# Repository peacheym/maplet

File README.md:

# Maplet

An ESP32 based eurorack module for libmapper connectivity.

## Why mappings in Eurorack?

Eurorack systems are excellent at making "generative music", where the system plays itself using sequencers, LFOs, clocks, and other modules. That said, there is lacking a method for "performative interaction" with Eurorack (asides from simply adjusting knobs directly on the system).

## Hardware

Maplet's front panel features a simple initial design.

## System Overview

The module uses an [UnexpectedMaker TinyPico](https://www.tinypico.com/) board based on the ESP32 chip as well as a MCP4728 digital-to-analog converter (DAC) as the main components.

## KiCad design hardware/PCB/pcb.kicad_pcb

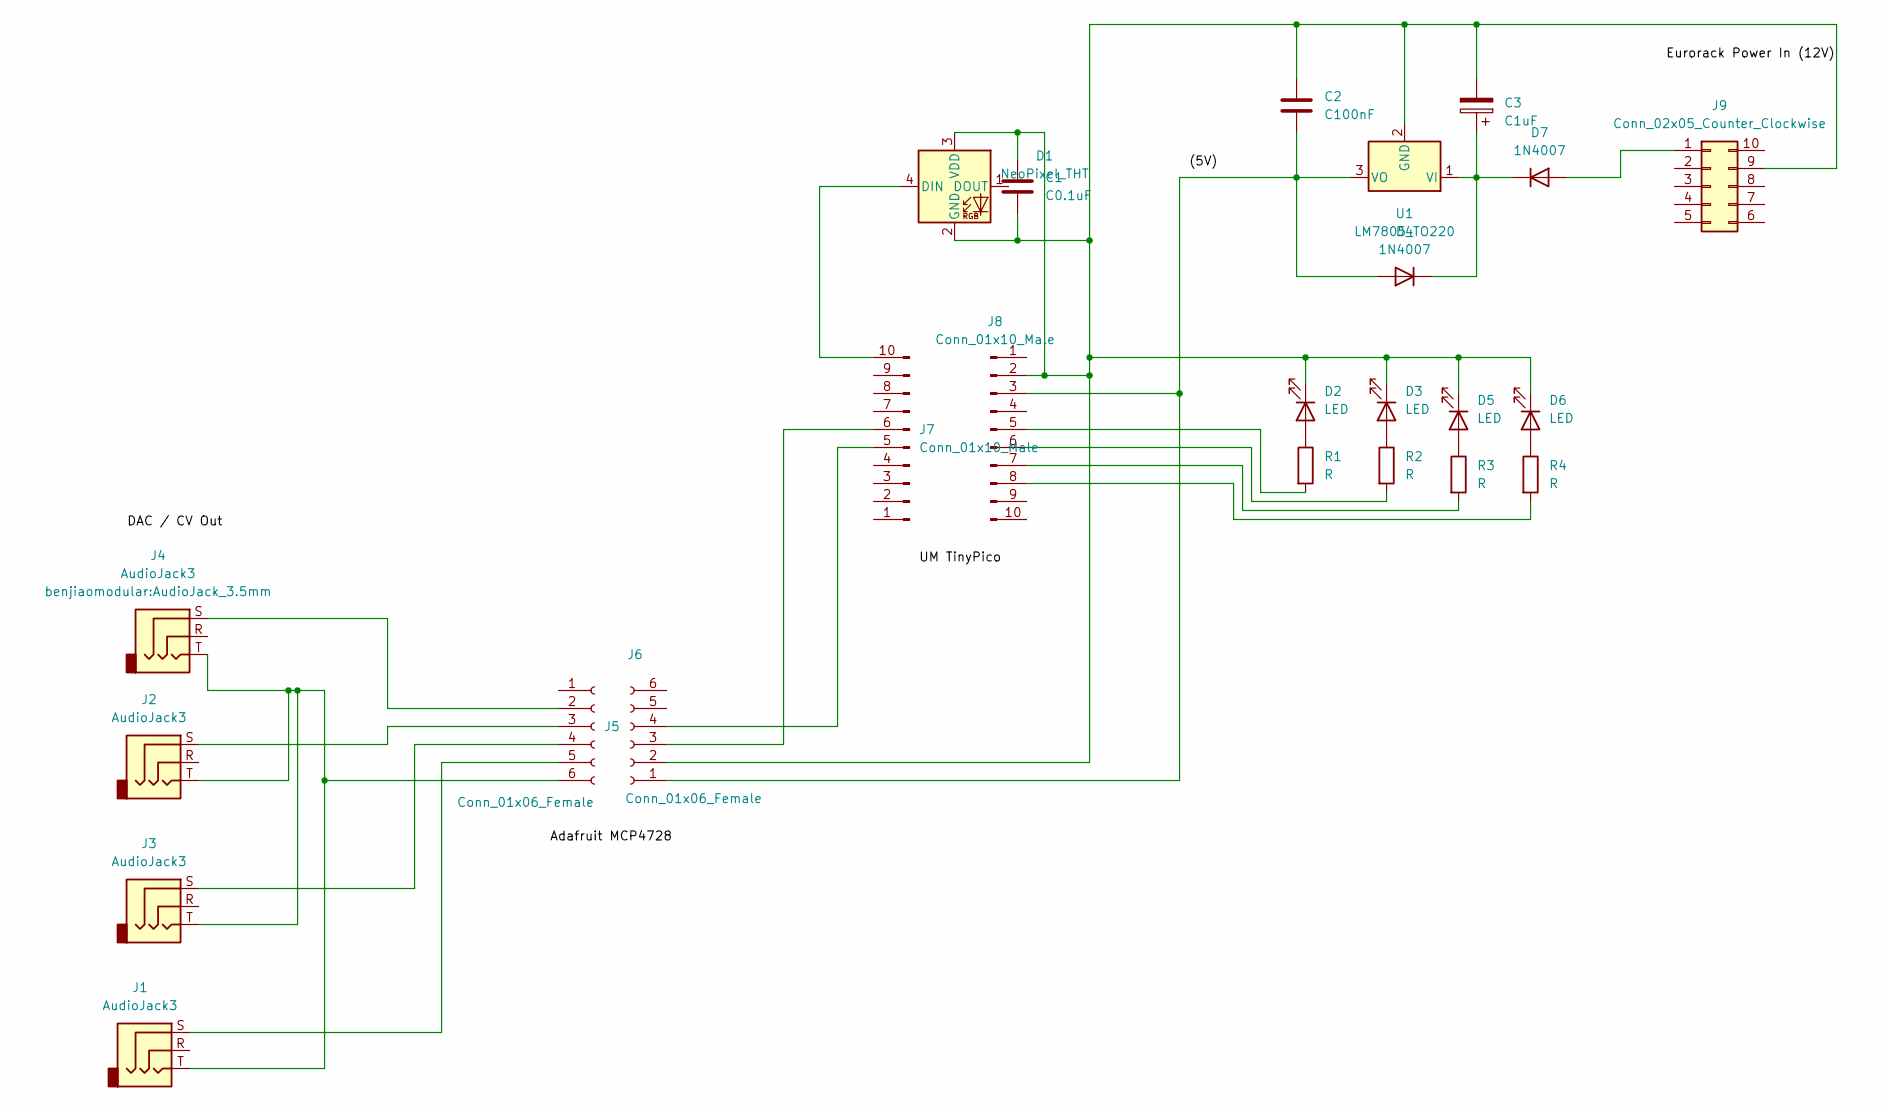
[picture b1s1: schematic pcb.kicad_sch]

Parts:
C1: C0.1uF; C_Rect_L4.0mm_W2.5mm_P2.50mm
C2: C100nF; C_Rect_L4.0mm_W2.5mm_P2.50mm
C3: C1uF; CP_Radial_D5.0mm_P2.50mm
D1: NeoPixel_THT; LED_D5.0mm-4_RGB_Staggered_Pins
D2, D3, D5, D6: LED; LED_D3.0mm
D4, D7: 1N4007; D_DO-41_SOD81_P10.16mm_Horizontal
J1, J2, J3, J4: AudioJack3; AudioJack_3.5mm
J5, J6: Conn_01x06_Female; PinSocket_1x06_P2.54mm_Vertical
J7, J8: Conn_01x10_Male; PinSocket_1x10_P2.54mm_Vertical
J9: Conn_02x05_Counter_Clockwise; IDC-Header_2x05_P2.54mm_Vertical
R1, R2, R3, R4: R; R_Axial_DIN0204_L3.6mm_D1.6mm_P2.54mm_Vertical
U1: LM7805_TO220; TO-220-3_Vertical

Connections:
unnamed: C1.1, C1.2, C2.1, C3.2, D1.2 (GND), D1.3 (VDD), D2.1 (K), D3.1 (K), D5.1 (K), D6.1 (K), J6.2, J8.2, J9.9, U1.2 (GND)
unnamed: C2.2, D4.2 (A), J6.1, J8.3, U1.3 (VO)
unnamed: C3.1, D4.1 (K), D7.1 (K), U1.1 (VI)
unnamed: D1.4 (DIN), J7.10
unnamed: D2.2 (A), R1.1
unnamed: D3.2 (A), R2.1
unnamed: D5.2 (A), R3.1
unnamed: D6.2 (A), R4.1
unnamed: D7.2 (A), J9.1
unnamed: J1.S, J5.5
unnamed: J2.S, J5.3
unnamed: J3.S, J5.4
unnamed: J4.S, J5.2
unnamed: J1.T, J2.T, J3.T, J4.T, J5.6
unnamed: J6.3, J7.6
unnamed: J6.4, J7.5
unnamed: J8.5, R1.2
unnamed: J8.6, R2.2
unnamed: J8.7, R3.2
unnamed: J8.8, R4.2

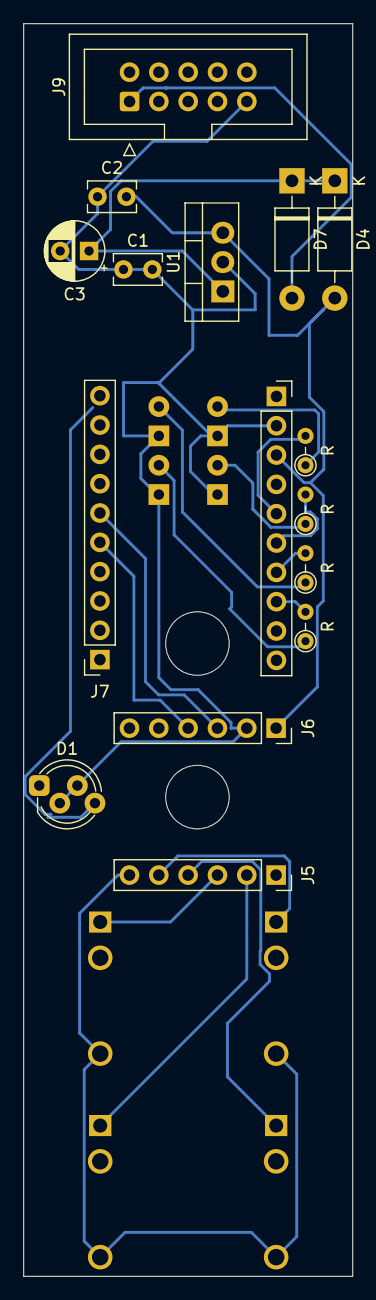
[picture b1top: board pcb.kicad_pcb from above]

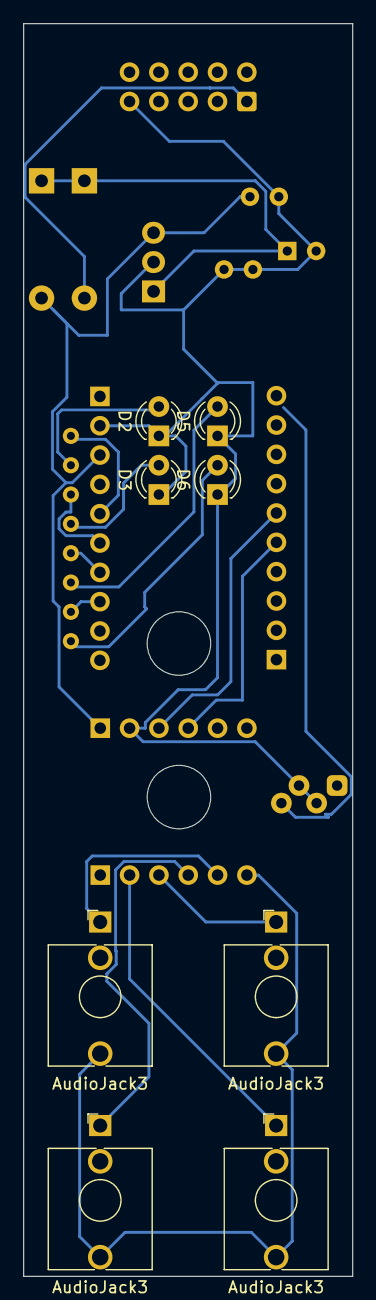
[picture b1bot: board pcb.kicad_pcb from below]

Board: 2 copper layers, 28.5 x 108.5 mm, 24 parts (8 on the bottom side), 20 nets.

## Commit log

2024-05-02 Commit firmware to repo
2024-05-02 update doc photo with non-transparent background
2024-05-02 update doc photo to be centered in page.
2024-05-02 Update README doc
2024-05-03 Add initial kicad files. Very much an experimental WIP
2024-07-31 Add second KiCad project for PCB
2024-08-08 Add latest KICAD updates.
2024-09-04 Add examples folder
2024-09-17 Update README.md in examples folder
2024-09-20 Add front panel image
2024-10-17 Push latest firmware
